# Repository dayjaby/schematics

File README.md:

Test board
==========

Goal: All parts in the desgin can be bought on jlcpcb

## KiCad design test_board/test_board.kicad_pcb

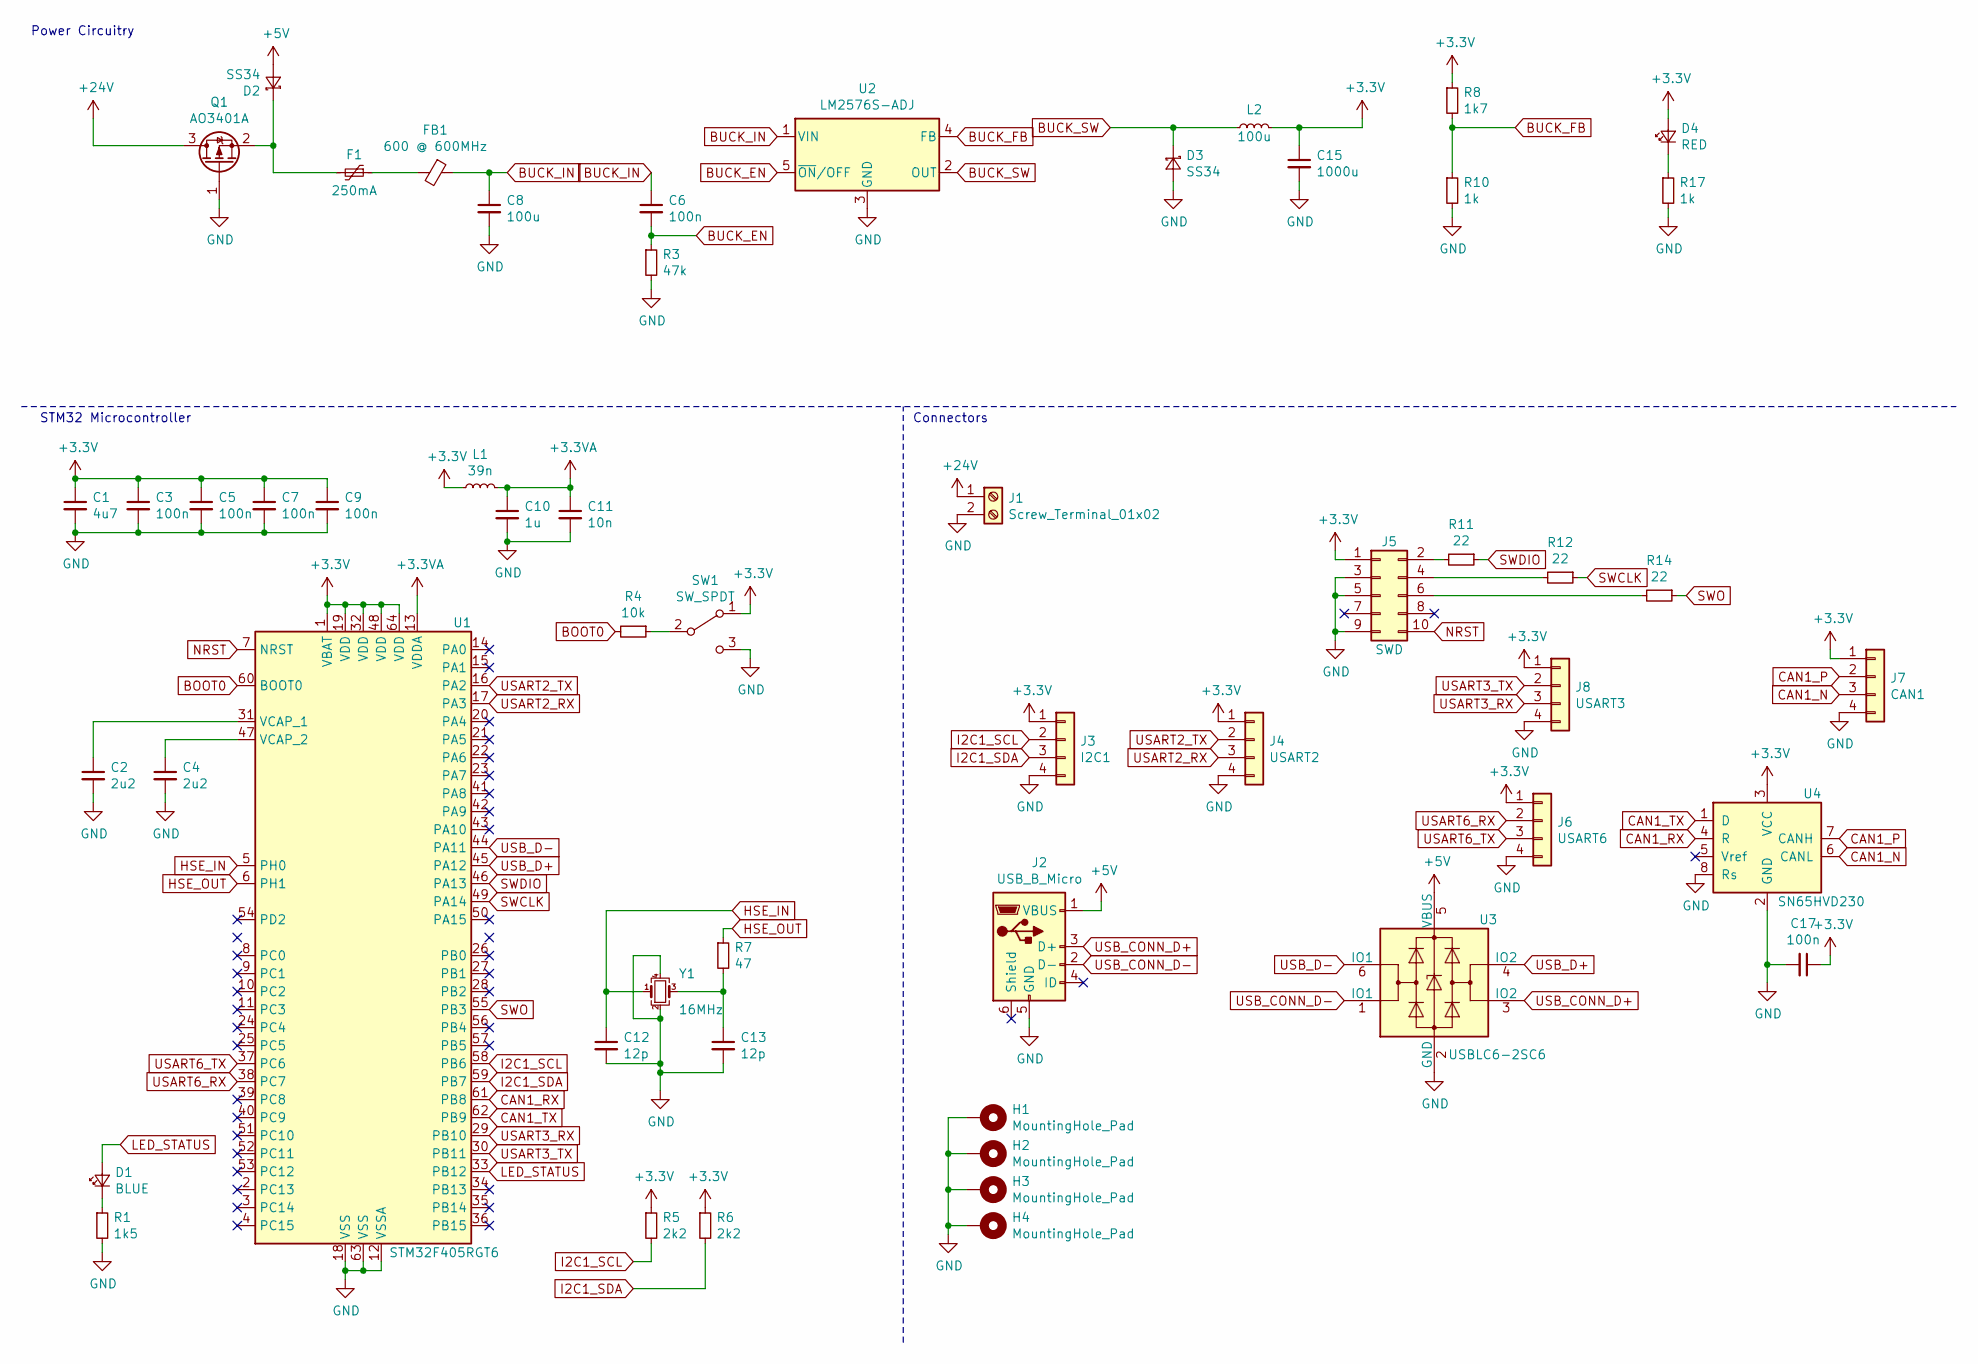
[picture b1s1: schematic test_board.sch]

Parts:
C1: 4u7; C_0603_1608Metric; LCSC Part # C19666
C2, C4: 2u2; C_0603_1608Metric; LCSC Part # C23630
C3, C5, C7, C9, C17: 100n; C_0402_1005Metric; LCSC Part # C1525
C6: 100n; C_1206_3216Metric; LCSC Part # C13585
C8: 100u; C_1206_3216Metric; LCSC Part # C13585
C10: 1u; C_0402_1005Metric; LCSC Part # C52923
C11: 10n; C_0402_1005Metric; LCSC Part # C15195
C12, C13: 12p; C_0402_1005Metric; LCSC Part # C1547
C15: 1000u; C_1206_3216Metric; LCSC Part # C13585
D1: BLUE; D_0603_1608Metric; LCSC Part # C72041
D2, D3: SS34; D_SMC; LCSC Part # C8598
D4: RED; D_0603_1608Metric; LCSC Part # C2286
F1: 250mA; Fuse_1206_3216Metric; LCSC Part # C369159
FB1: 600 @ 600MHz; L_0805_2012Metric; LCSC Part # C1017
H1, H2, H3, H4: MountingHole_Pad; MountingHole_4.3mm_M4_Pad_Via
J1: Screw_Terminal_01x02; TerminalBlock_Phoenix_PT-1,5-2-5.0-H_1x02_P5.00mm_Horizontal
J2: USB_B_Micro; USB_Micro-B_Wuerth_629105150521
J3: I2C1; PinHeader_1x04_P2.54mm_Vertical
J4: USART2; PinHeader_1x04_P2.54mm_Vertical
J5: SWD; PinHeader_2x05_P2.54mm_Vertical
J6: USART6; PinHeader_1x04_P2.54mm_Vertical
J7: CAN1; PinHeader_1x04_P2.54mm_Vertical
J8: USART3; PinHeader_1x04_P2.54mm_Vertical
L1: 39n; L_0402_1005Metric; LCSC Part # C26443
L2: 100u; L_Sunlord_MWSA0518_5.4x5.2mm; LCSC Part # C139506
Q1: AO3401A; SOT-23; LCSC Part # C15127
R1: 1k5; R_0603_1608Metric; LCSC Part # C22843
R3: 47k; R_0603_1608Metric; LCSC Part # C23231
R4: 10k; R_0402_1005Metric; LCSC Part # C25744
R5, R6: 2k2; R_0603_1608Metric; LCSC Part # C25879
R7: 47; R_0402_1005Metric; LCSC Part # C25118
R8: 1k7; R_0603_1608Metric; LCSC Part # C25819
R10: 1k; R_0603_1608Metric; LCSC Part # C22966
R11, R12, R14: 22; R_0402_1005Metric; LCSC Part # C25092
R17: 1k; R_0603_1608Metric; LCSC Part # C21190
SW1: SW_SPDT; SW_SPDT_PCM12
U1: STM32F405RGT6; LQFP-64_10x10mm_P0.5mm; LCSC Part # C15742
U2: LM2576S-ADJ; TO-263-5_TabPin3
U3: USBLC6-2SC6; SOT-23-6; LCSC Part # C7519
U4: SN65HVD230; SOIC-8_3.9x4.9mm_P1.27mm; LCSC Part # C12084
Y1: 16MHz; Crystal_SMD_3225-4Pin_3.2x2.5mm; LCSC Part # C13738

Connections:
+3.3VA: C10.1, C11.1, L1.2, U1.13 (VDDA)
+3V3: C1.1, C3.1, C5.1, C7.1, C9.1, C15.1, C17.1, D4.2 (A), J3.1, J4.1, J5.1, J6.1, J7.1, J8.1, L1.1, L2.2, R5.1, R6.1, R8.1, SW1.1 (A), U1.1 (VBAT), U1.19 (VDD), U1.32 (VDD), U1.48 (VDD), U1.64 (VDD), U4.3 (VCC)
+5V: D2.2 (A), J2.1 (VBUS), U3.5 (VBUS)
+24V: J1.1, Q1.3 (D)
BOOT0: R4.2, U1.60 (BOOT0)
BUCK_EN: C6.2, R3.1, U2.5 (~ON~/OFF)
BUCK_FB: R8.2, R10.1, U2.4 (FB)
BUCK_IN: C6.1, C8.1, FB1.1, U2.1 (VIN)
BUCK_SW: D3.1 (K), L2.1, U2.2 (OUT)
CAN1_N: J7.3, U4.6 (CANL)
CAN1_P: J7.2, U4.7 (CANH)
CAN1_RX: U1.61 (PB8), U4.4 (R)
CAN1_TX: U1.62 (PB9), U4.1 (D)
GND: C1.2, C2.2, C3.2, C4.2, C5.2, C7.2, C8.2, C9.2, C10.2, C11.2, C12.2, C13.2, C15.2, C17.2, D3.2 (A), H1.1, H2.1, H3.1, H4.1, J1.2, J2.5 (GND), J3.4, J4.4, J5.3, J5.5, J5.9, J6.4, J7.4, J8.4, Q1.1 (G), R1.2, R3.2, R10.2, R17.2, SW1.3 (C), U1.12 (VSSA), U1.18 (VSS), U1.63 (VSS), U2.3 (GND), U3.2 (GND), U4.2 (GND), U4.8 (Rs), Y1.2, Y1.4
HSE_IN: C12.1, U1.5 (PH0), Y1.1
HSE_OUT: R7.1, U1.6 (PH1)
I2C1_SCL: J3.2, R5.2, U1.58 (PB6)
I2C1_SDA: J3.3, R6.2, U1.59 (PB7)
LED_STATUS: D1.2 (A), U1.33 (PB12)
NRST: J5.10, U1.7 (NRST)
unnamed: C2.1, U1.31 (VCAP_1)
unnamed: C4.1, U1.47 (VCAP_2)
unnamed: C13.1, R7.2, Y1.3
unnamed: D1.1 (K), R1.1
unnamed: D2.1 (K), F1.2, Q1.2 (S)
unnamed: D4.1 (K), R17.1
unnamed: F1.1, FB1.2
unnamed: J5.2, R11.2
unnamed: J5.4, R12.2
unnamed: J5.6, R14.2
unnamed: R4.1, SW1.2 (B)
SWCLK: R12.1, U1.49 (PA14)
SWDIO: R11.1, U1.46 (PA13)
SWO: R14.1, U1.55 (PB3)
USART2_RX: J4.3, U1.17 (PA3)
USART2_TX: J4.2, U1.16 (PA2)
USART3_RX: J8.3, U1.29 (PB10)
USART3_TX: J8.2, U1.30 (PB11)
USART6_RX: J6.2, U1.38 (PC7)
USART6_TX: J6.3, U1.37 (PC6)
USB_CONN_D+: J2.3 (D+), U3.3 (IO2)
USB_CONN_D-: J2.2 (D-), U3.1 (IO1)
USB_D+: U1.45 (PA12), U3.4 (IO2)
USB_D-: U1.44 (PA11), U3.6 (IO1)

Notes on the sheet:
STM32 Microcontroller
Connectors
Power Circuitry

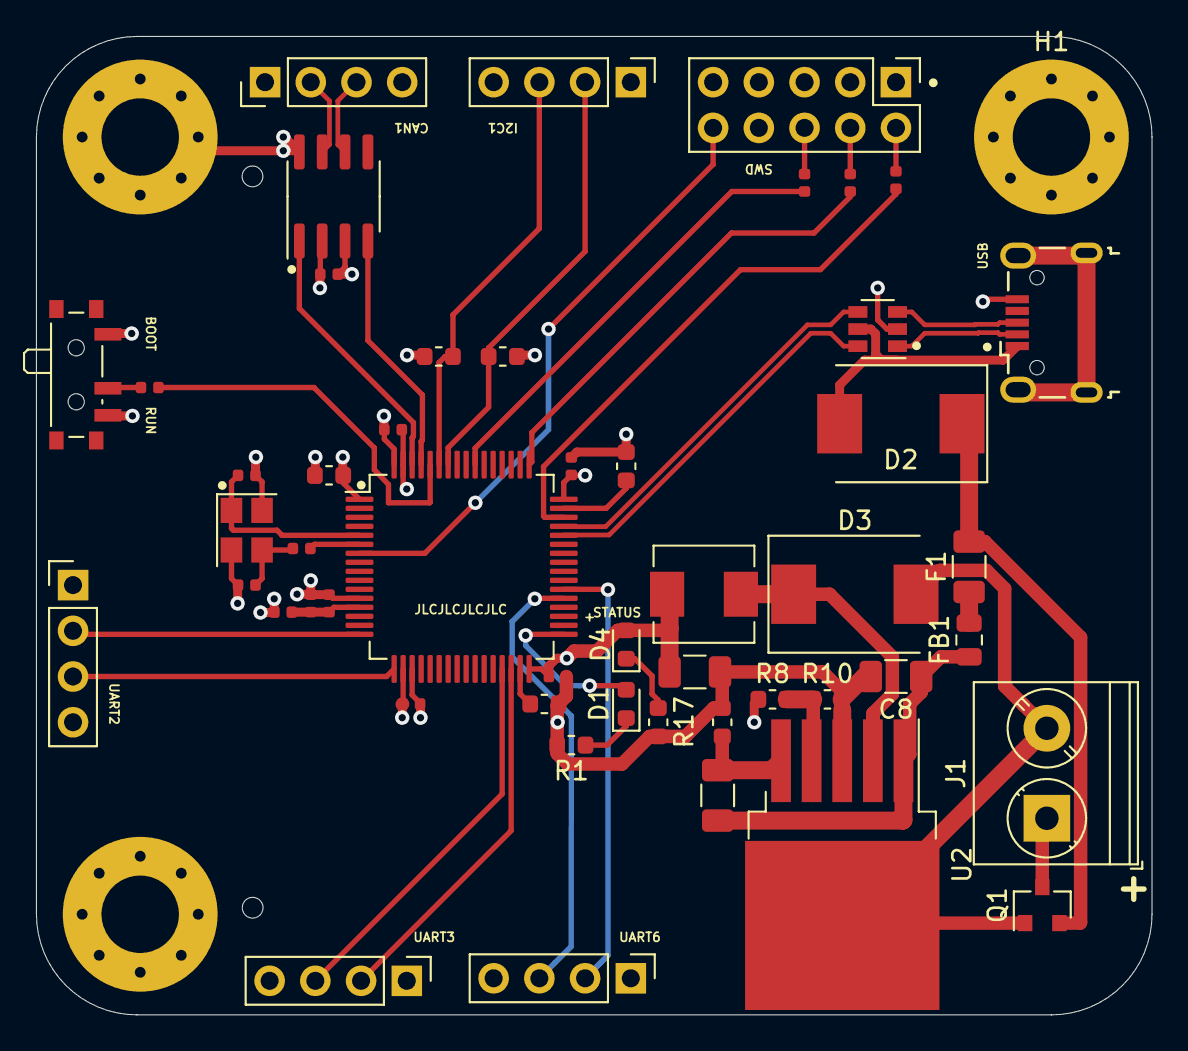
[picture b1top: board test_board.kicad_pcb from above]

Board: 4 copper layers, 62.0 x 54.4 mm, 53 parts (0 on the bottom side), 44 nets.

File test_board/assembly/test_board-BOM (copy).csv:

Comment,Designator,Footprint,LCSC Part #
"4u7 Unpolarized capacitor, small symbol",C1,C_0603_1608Metric,
"2u2 Unpolarized capacitor, small symbol","C2,C4",C_0603_1608Metric,
"100n Unpolarized capacitor, small symbol","C3,C5,C7,C9,C17",C_0402_1005Metric,
"10u Unpolarized capacitor, small symbol","C8,C15,C16",C_1206_3216Metric,
"1u Unpolarized capacitor, small symbol",C10,C_0402_1005Metric,
"10n Unpolarized capacitor, small symbol",C11,C_0402_1005Metric,
"12p Unpolarized capacitor, small symbol","C12,C13",C_0402_1005Metric,
"10n Unpolarized capacitor, small symbol",C14,C_1206_3216Metric,
"BLUE Light emitting diode, small symbol",D1,D_0603_1608Metric,
"B5819W Schottky diode, small symbol","D2,D3",D_SOD-123,
"RED Light emitting diode, small symbol",D4,D_0603_1608Metric,
"250mA Resettable fuse, polymeric positive temperature coefficient, small symbol",F1,Fuse_1206_3216Metric,
"600 @ 600MHz Ferrite bead, small symbol",FB1,L_0805_2012Metric,
MountingHole_Pad Mounting Hole with connection,"H1,H2,H3,H4",MountingHole_4.3mm_M4_Pad_Via,
"Screw_Terminal_01x02 Generic screw terminal, single row, 01x02, script generated (kicad-library-utils/schlib/autogen/connector/)",J1,"TerminalBlock_Phoenix_PT-1,5-2-5.0-H_1x02_P5.00mm_Horizontal",
USB_B_Micro USB Micro Type B connector,J2,USB_Micro-B_Wuerth_629105150521,
"I2C1 Generic connector, single row, 01x04, script generated (kicad-library-utils/schlib/autogen/connector/)",J3,PinHeader_1x04_P2.54mm_Vertical,
"USART2 Generic connector, single row, 01x04, script generated (kicad-library-utils/schlib/autogen/connector/)",J4,PinHeader_1x04_P2.54mm_Vertical,
"SWD Generic connector, double row, 02x05, odd/even pin numbering scheme (row 1 odd numbers, row 2 even numbers), script generated (kicad-library-utils/schlib/autogen/connector/)",J5,PinHeader_2x05_P2.54mm_Vertical,
"USART6 Generic connector, single row, 01x04, script generated (kicad-library-utils/schlib/autogen/connector/)",J6,PinHeader_1x04_P2.54mm_Vertical,
"CAN1 Generic connector, single row, 01x04, script generated (kicad-library-utils/schlib/autogen/connector/)",J7,PinHeader_1x04_P2.54mm_Vertical,
"USART3 Generic connector, single row, 01x04, script generated (kicad-library-utils/schlib/autogen/connector/)",J8,PinHeader_1x04_P2.54mm_Vertical,
"39n Inductor, small symbol",L1,L_0402_1005Metric,
"10u Inductor, small symbol",L2,L_Sunlord_MWSA0518_5.4x5.2mm,
"AO3401A -4.0A Id, -30V Vds, P-Channel MOSFET, SOT-23",Q1,SOT-23,
"1k5 Resistor, small symbol",R1,R_0603_1608Metric,
"100k Resistor, small symbol",R2,R_0603_1608Metric,
"68k Resistor, small symbol",R3,R_0603_1608Metric,
"10k Resistor, small symbol",R4,R_0402_1005Metric,
"2k2 Resistor, small symbol","R5,R6",R_0603_1608Metric,
"47 Resistor, small symbol",R7,R_0402_1005Metric,
"47k Resistor, small symbol",R8,R_0603_1608Metric,
"15k Resistor, small symbol",R9,R_0603_1608Metric,
"270 Resistor, small symbol",R10,R_0603_1608Metric,
"22 Resistor, small symbol","R11,R12,R14",R_0402_1005Metric,
"1k Resistor, small symbol",R17,R_0603_1608Metric,
"SW_SPDT Switch, single pole double throw",SW1,SW_SPDT_PCM12,
"STM32F405RGT6 ARM Cortex-M4 MCU, 1024KB flash, 128KB RAM, 168MHz, 1.8-3.6V, 51 GPIO, LQFP-64",U1,LQFP-64_10x10mm_P0.5mm,
MP2359DJ-LF-Z ,U2,SOIC127P599X175-8N,
"USBLC6-2SC6 Bidirectional ESD Protection Diode, SOT-23-6",U3,SOT-23-6,
"SN65HVD230 CAN Bus Transceivers, 3.3V, 1Mbps, Low-Power capabilities, SOIC",U4,SOIC-8_3.9x4.9mm_P1.27mm,
"16MHz Four pin crystal, GND on pins 2 and 4, small symbol",Y1,Crystal_SMD_3225-4Pin_3.2x2.5mm,

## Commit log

2021-03-11 added STM32 test board
2021-03-11 added README.md
2021-03-12 Replace MD3579DJ with LM2576-ADJ
2021-03-13 added ftdi4232h board
2021-03-17 Use TPD2E2U06 as ESD protection for USB
    The PCB design seems much more natural for USB using this IC compared to
    alternatives.
